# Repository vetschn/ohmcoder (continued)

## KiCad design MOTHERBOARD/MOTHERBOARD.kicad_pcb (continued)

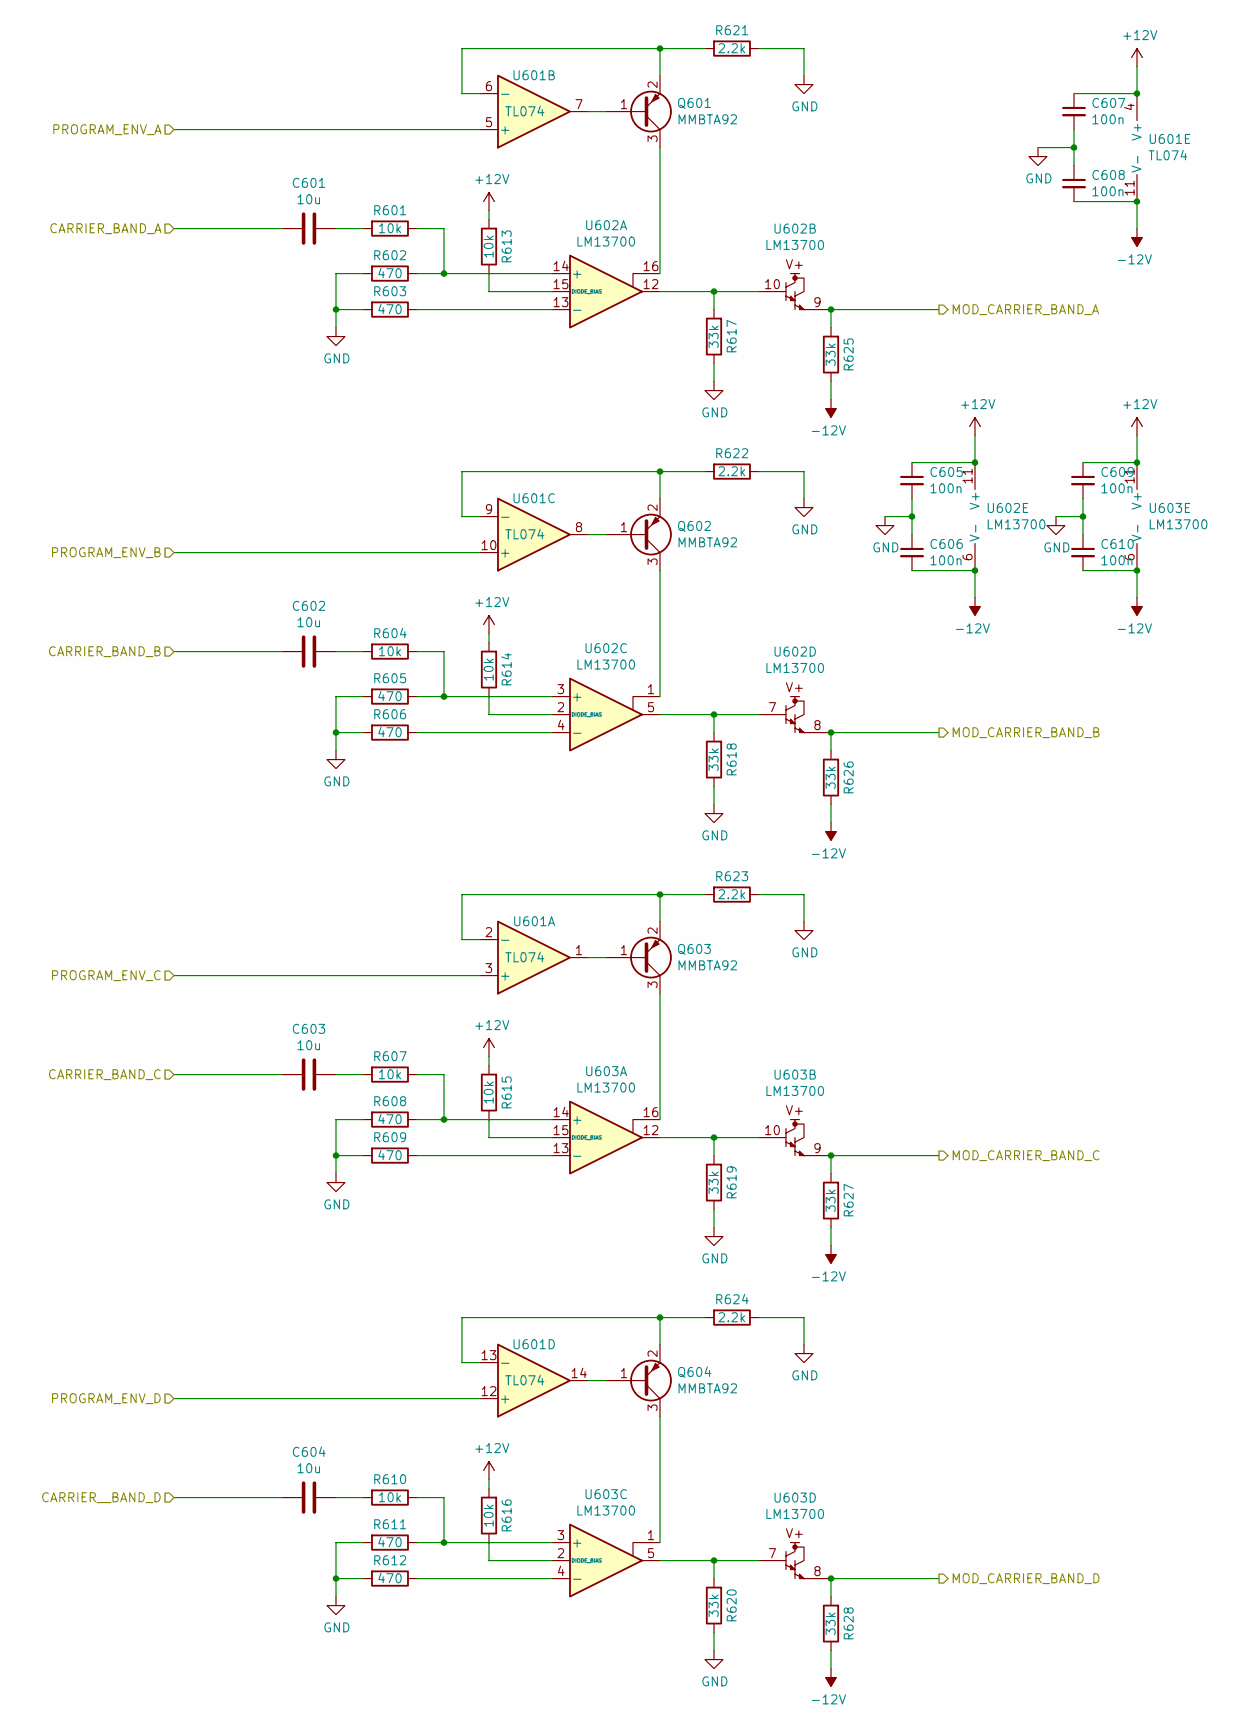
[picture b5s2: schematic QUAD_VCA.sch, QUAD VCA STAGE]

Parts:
C301, C302, C303, C304: 10u; C_0603_1608Metric_Pad1.08x0.95mm_HandSolder
C305, C306, C307, C308, C309, C310: 100n; C_0603_1608Metric_Pad1.08x0.95mm_HandSolder
Q301, Q302, Q303, Q304: MMBTA92; SOT-23
R301, R304, R307, R310, R313, R314, R315, R316: 10k; R_0603_1608Metric_Pad0.98x0.95mm_HandSolder
R302, R303, R305, R306, R308, R309, R311, R312: 470; R_0603_1608Metric_Pad0.98x0.95mm_HandSolder
R317, R318, R319, R320, R325, R326, R327, R328: 33k; R_0603_1608Metric_Pad0.98x0.95mm_HandSolder
R321, R322, R323, R324: 2.2k; R_0603_1608Metric_Pad0.98x0.95mm_HandSolder
U301: TL074; TL074-SOIC-14
U302, U303: LM13700; LM13700-SOIC-16

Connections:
+12V: C305.1, C307.1, C309.1, R313.2, R314.2, R315.2, R316.2, U301.4 (V+), U302.11 (V+), U303.11 (V+); also elsewhere on the board
/CARRIER_BAND_1: C301.2; also elsewhere on the board
/CARRIER_BAND_2: C302.2; also elsewhere on the board
/CARRIER_BAND_3: C303.2; also elsewhere on the board
/CARRIER_BAND_4: C304.2; also elsewhere on the board
/MOD_CARRIER_BAND_1: R325.2, U302.9; also elsewhere on the board
/MOD_CARRIER_BAND_2: R326.2, U302.8; also elsewhere on the board
/MOD_CARRIER_BAND_3: R327.2, U303.9; also elsewhere on the board
/MOD_CARRIER_BAND_4: R328.2, U303.8; also elsewhere on the board
/PROGRAM_ENV_1: U301.5 (+); also elsewhere on the board
/PROGRAM_ENV_2: U301.10 (+); also elsewhere on the board
/PROGRAM_ENV_3: U301.3 (+); also elsewhere on the board
/PROGRAM_ENV_4: U301.12 (+); also elsewhere on the board
GND: C305.2, C306.1, C307.2, C308.1, C309.2, C310.1, R302.2, R303.2, R305.2, R306.2, R308.2, R309.2, R311.2, R312.2, R317.1, R318.1, R319.1, R320.1, R321.1, R322.1, R323.1, R324.1; also elsewhere on the board
unnamed: C301.1, R301.2
unnamed: C302.1, R304.2
unnamed: C303.1, R307.2
unnamed: C304.1, R310.2
unnamed: Q301.1 (B), U301.7
unnamed: Q301.2 (E), R321.2, U301.6 (-)
unnamed: Q301.3 (C), U302.16
unnamed: Q302.1 (B), U301.8
unnamed: Q302.2 (E), R322.2, U301.9 (-)
unnamed: Q302.3 (C), U302.1
unnamed: Q303.1 (B), U301.1
unnamed: Q303.2 (E), R323.2, U301.2 (-)
unnamed: Q303.3 (C), U303.16
unnamed: Q304.1 (B), U301.14
unnamed: Q304.2 (E), R324.2, U301.13 (-)
unnamed: Q304.3 (C), U303.1
unnamed: R301.1, R302.1, U302.14 (+)
unnamed: R303.1, U302.13 (-)
unnamed: R304.1, R305.1, U302.3 (+)
unnamed: R306.1, U302.4 (-)
unnamed: R307.1, R308.1, U303.14 (+)
unnamed: R309.1, U303.13 (-)
unnamed: R310.1, R311.1, U303.3 (+)
unnamed: R312.1, U303.4 (-)
unnamed: R313.1, U302.15 (DIODE_BIAS)
unnamed: R314.1, U302.2 (DIODE_BIAS)
unnamed: R315.1, U303.15 (DIODE_BIAS)
unnamed: R316.1, U303.2 (DIODE_BIAS)
unnamed: R317.2, U302.10, U302.12
unnamed: R318.2, U302.5, U302.7
unnamed: R319.2, U303.10, U303.12
unnamed: R320.2, U303.5, U303.7

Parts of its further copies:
C401, C402, C403, C404, C501, C502, C503, C504, C601, C602, C603, C604: 10u; C_0603_1608Metric_Pad1.08x0.95mm_HandSolder
C405, C406, C407, C408, C409, C410, C505, C506, C507, C508, C509, C510, C605, C606, C607, C608, C609, C610: 100n; C_0603_1608Metric_Pad1.08x0.95mm_HandSolder
Q401, Q402, Q403, Q404, Q501, Q502, Q503, Q504, Q601, Q602, Q603, Q604: MMBTA92; SOT-23
R401, R404, R407, R410, R413, R414, R415, R416, R501, R504, R507, R510, R513, R514, R515, R516, R601, R604, R607, R610, R613, R614, R615, R616: 10k; R_0603_1608Metric_Pad0.98x0.95mm_HandSolder
R402, R403, R405, R406, R408, R409, R411, R412, R502, R503, R505, R506, R508, R509, R511, R512, R602, R603, R605, R606, R608, R609, R611, R612: 470; R_0603_1608Metric_Pad0.98x0.95mm_HandSolder
R417, R418, R419, R420, R425, R426, R427, R428, R517, R518, R519, R520, R525, R526, R527, R528, R617, R618, R619, R620, R625, R626, R627, R628: 33k; R_0603_1608Metric_Pad0.98x0.95mm_HandSolder
R421, R422, R423, R424, R521, R522, R523, R524, R621, R622, R623, R624: 2.2k; R_0603_1608Metric_Pad0.98x0.95mm_HandSolder
U401, U501, U601: TL074; TL074-SOIC-14
U402, U403, U502, U503, U602, U603: LM13700; LM13700-SOIC-16

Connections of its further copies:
+12V: C405.1, C407.1, C409.1, C505.1, C507.1, C509.1, C605.1, C607.1, C609.1, R413.2, R414.2, R415.2, R416.2, R513.2, R514.2, R515.2, R516.2, R613.2, R614.2, R615.2, R616.2, U401.4 (V+), U402.11 (V+), U403.11 (V+), U501.4 (V+), U502.11 (V+), U503.11 (V+), U601.4 (V+), U602.11 (V+), U603.11 (V+); also elsewhere on the board
/CARRIER_BAND_5: C401.2; also elsewhere on the board
/CARRIER_BAND_6: C402.2; also elsewhere on the board
/CARRIER_BAND_7: C403.2; also elsewhere on the board
/CARRIER_BAND_8: C404.2; also elsewhere on the board
/CARRIER_BAND_9: C501.2; also elsewhere on the board
/CARRIER_BAND_10: C502.2; also elsewhere on the board
/CARRIER_BAND_11: C503.2; also elsewhere on the board
/CARRIER_BAND_12: C504.2; also elsewhere on the board
/CARRIER_BAND_13: C601.2; also elsewhere on the board
/CARRIER_BAND_14: C602.2; also elsewhere on the board
/CARRIER_BAND_15: C603.2; also elsewhere on the board
/CARRIER_BAND_16: C604.2; also elsewhere on the board
/MOD_CARRIER_BAND_5: R425.2, U402.9; also elsewhere on the board
/MOD_CARRIER_BAND_6: R426.2, U402.8; also elsewhere on the board
/MOD_CARRIER_BAND_7: R427.2, U403.9; also elsewhere on the board
/MOD_CARRIER_BAND_8: R428.2, U403.8; also elsewhere on the board
/MOD_CARRIER_BAND_9: R525.2, U502.9; also elsewhere on the board
/MOD_CARRIER_BAND_10: R526.2, U502.8; also elsewhere on the board
/MOD_CARRIER_BAND_11: R527.2, U503.9; also elsewhere on the board
/MOD_CARRIER_BAND_12: R528.2, U503.8; also elsewhere on the board
/MOD_CARRIER_BAND_13: R625.2, U602.9; also elsewhere on the board
/MOD_CARRIER_BAND_14: R626.2, U602.8; also elsewhere on the board
/MOD_CARRIER_BAND_15: R627.2, U603.9; also elsewhere on the board
/MOD_CARRIER_BAND_16: R628.2, U603.8; also elsewhere on the board
/PROGRAM_ENV_5: U401.5 (+); also elsewhere on the board
/PROGRAM_ENV_6: U401.10 (+); also elsewhere on the board
/PROGRAM_ENV_7: U401.3 (+); also elsewhere on the board
/PROGRAM_ENV_8: U401.12 (+); also elsewhere on the board
/PROGRAM_ENV_9: U501.5 (+); also elsewhere on the board
/PROGRAM_ENV_10: U501.10 (+); also elsewhere on the board
/PROGRAM_ENV_11: U501.3 (+); also elsewhere on the board
/PROGRAM_ENV_12: U501.12 (+); also elsewhere on the board
/PROGRAM_ENV_13: U601.5 (+); also elsewhere on the board
/PROGRAM_ENV_14: U601.10 (+); also elsewhere on the board
/PROGRAM_ENV_15: U601.3 (+); also elsewhere on the board
/PROGRAM_ENV_16: U601.12 (+); also elsewhere on the board
GND: C405.2, C406.1, C407.2, C408.1, C409.2, C410.1, C505.2, C506.1, C507.2, C508.1, C509.2, C510.1, C605.2, C606.1, C607.2, C608.1, C609.2, C610.1, R402.2, R403.2, R405.2, R406.2, R408.2, R409.2, R411.2, R412.2, R417.1, R418.1, R419.1, R420.1, R421.1, R422.1, R423.1, R424.1, R502.2, R503.2, R505.2, R506.2, R508.2, R509.2, R511.2, R512.2, R517.1, R518.1, R519.1, R520.1, R521.1, R522.1, R523.1, R524.1, R602.2, R603.2, R605.2, R606.2, R608.2, R609.2, R611.2, R612.2, R617.1, R618.1, R619.1, R620.1, R621.1, R622.1, R623.1, R624.1; also elsewhere on the board
unnamed: C401.1, R401.2
unnamed: C402.1, R404.2
unnamed: C403.1, R407.2
unnamed: C404.1, R410.2
unnamed: C501.1, R501.2
unnamed: C502.1, R504.2
unnamed: C503.1, R507.2
unnamed: C504.1, R510.2
unnamed: C601.1, R601.2
unnamed: C602.1, R604.2
unnamed: C603.1, R607.2
unnamed: C604.1, R610.2
unnamed: Q401.1 (B), U401.7
unnamed: Q401.2 (E), R421.2, U401.6 (-)
unnamed: Q401.3 (C), U402.16
unnamed: Q402.1 (B), U401.8
unnamed: Q402.2 (E), R422.2, U401.9 (-)
unnamed: Q402.3 (C), U402.1
unnamed: Q403.1 (B), U401.1
unnamed: Q403.2 (E), R423.2, U401.2 (-)
unnamed: Q403.3 (C), U403.16
unnamed: Q404.1 (B), U401.14
unnamed: Q404.2 (E), R424.2, U401.13 (-)
unnamed: Q404.3 (C), U403.1
unnamed: Q501.1 (B), U501.7
unnamed: Q501.2 (E), R521.2, U501.6 (-)
unnamed: Q501.3 (C), U502.16
unnamed: Q502.1 (B), U501.8
unnamed: Q502.2 (E), R522.2, U501.9 (-)
unnamed: Q502.3 (C), U502.1
unnamed: Q503.1 (B), U501.1
unnamed: Q503.2 (E), R523.2, U501.2 (-)
unnamed: Q503.3 (C), U503.16
unnamed: Q504.1 (B), U501.14
unnamed: Q504.2 (E), R524.2, U501.13 (-)
unnamed: Q504.3 (C), U503.1
unnamed: Q601.1 (B), U601.7
unnamed: Q601.2 (E), R621.2, U601.6 (-)
unnamed: Q601.3 (C), U602.16
unnamed: Q602.1 (B), U601.8
unnamed: Q602.2 (E), R622.2, U601.9 (-)
unnamed: Q602.3 (C), U602.1
unnamed: Q603.1 (B), U601.1
unnamed: Q603.2 (E), R623.2, U601.2 (-)
unnamed: Q603.3 (C), U603.16
unnamed: Q604.1 (B), U601.14
unnamed: Q604.2 (E), R624.2, U601.13 (-)
unnamed: Q604.3 (C), U603.1
unnamed: R401.1, R402.1, U402.14 (+)
unnamed: R403.1, U402.13 (-)
unnamed: R404.1, R405.1, U402.3 (+)
unnamed: R406.1, U402.4 (-)
unnamed: R407.1, R408.1, U403.14 (+)
unnamed: R409.1, U403.13 (-)
unnamed: R410.1, R411.1, U403.3 (+)
unnamed: R412.1, U403.4 (-)
unnamed: R413.1, U402.15 (DIODE_BIAS)
unnamed: R414.1, U402.2 (DIODE_BIAS)
unnamed: R415.1, U403.15 (DIODE_BIAS)
unnamed: R416.1, U403.2 (DIODE_BIAS)
unnamed: R417.2, U402.10, U402.12
unnamed: R418.2, U402.5, U402.7
unnamed: R419.2, U403.10, U403.12
unnamed: R420.2, U403.5, U403.7
unnamed: R501.1, R502.1, U502.14 (+)
unnamed: R503.1, U502.13 (-)
unnamed: R504.1, R505.1, U502.3 (+)
unnamed: R506.1, U502.4 (-)
unnamed: R507.1, R508.1, U503.14 (+)
unnamed: R509.1, U503.13 (-)
unnamed: R510.1, R511.1, U503.3 (+)
unnamed: R512.1, U503.4 (-)
unnamed: R513.1, U502.15 (DIODE_BIAS)
unnamed: R514.1, U502.2 (DIODE_BIAS)
unnamed: R515.1, U503.15 (DIODE_BIAS)
unnamed: R516.1, U503.2 (DIODE_BIAS)
unnamed: R517.2, U502.10, U502.12
unnamed: R518.2, U502.5, U502.7
unnamed: R519.2, U503.10, U503.12
unnamed: R520.2, U503.5, U503.7
unnamed: R601.1, R602.1, U602.14 (+)
unnamed: R603.1, U602.13 (-)
unnamed: R604.1, R605.1, U602.3 (+)
unnamed: R606.1, U602.4 (-)
unnamed: R607.1, R608.1, U603.14 (+)
unnamed: R609.1, U603.13 (-)
unnamed: R610.1, R611.1, U603.3 (+)
unnamed: R612.1, U603.4 (-)
unnamed: R613.1, U602.15 (DIODE_BIAS)
unnamed: R614.1, U602.2 (DIODE_BIAS)
unnamed: R615.1, U603.15 (DIODE_BIAS)
unnamed: R616.1, U603.2 (DIODE_BIAS)
unnamed: R617.2, U602.10, U602.12
unnamed: R618.2, U602.5, U602.7
unnamed: R619.2, U603.10, U603.12
unnamed: R620.2, U603.5, U603.7

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
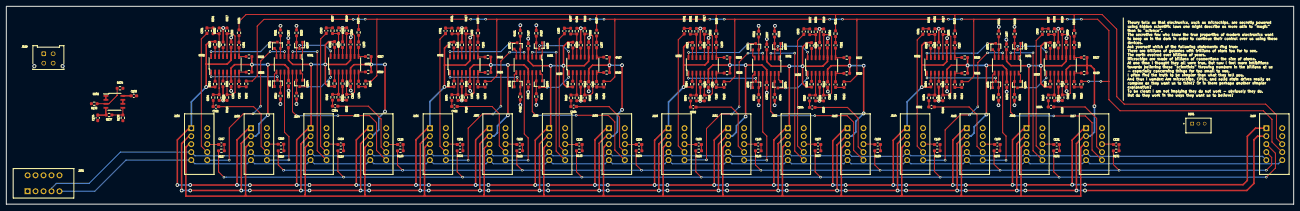
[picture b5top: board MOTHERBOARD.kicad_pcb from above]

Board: 2 copper layers, 410.0 x 63.0 mm, 271 parts (0 on the bottom side), 237 nets.

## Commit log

2021-11-23 Routed all the hard parts
2021-12-12 New series resistor values for LEDs
2022-01-26 More documentation
2022-01-26 No LaTeX in GitHub markdown
2022-01-28 Major folder restructuring
2022-01-28 PDFs of schematics
